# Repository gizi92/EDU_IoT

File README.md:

# EDU_IoT
## UBB IoT  project - Smart Office

### Project structure
- NodeMCU:
    - Up to date version: `/mcus/nodemcu/spi_master`
    - Example code snippets: `/mcus/nodemcu/examples/`
    - To run the examples, you need to install the following libraries:
        - LittleFS by lorol: https://github.com/lorol/LITTLEFS
        - ESP8266WiFi: https://github.com/esp8266/Arduino/tree/master/libraries/ESP8266WiFi
        - ESPAsyncTCP by me-no-dev: https://github.com/me-no-dev/ESPAsyncTCP
        - ESPAsyncWebServer by me-no-dev: https://github.com/me-no-dev/ESPAsyncWebServer
        - Arduino_JSON by arduino-libraries: https://github.com/arduino-libraries/Arduino_JSON
        - PubSubClient by knolleary: https://github.com/knolleary/pubsubclient

- Arduino Uno:
    - Up to date version: `/mcus/arduino_uno/spi_slave`
    - Example code snippets: `/mcus/arduino_uno/examples/`
    - To run the examples, you need to install the following libraries:
        - LiquidCrystal I2C by Marco Schwartz: https://github.com/johnrickman/LiquidCrystal_I2C
        - Arduino-DS3231 by Korneliusz Jarzebski: https://github.com/jarzebski/Arduino-DS3231
        - SimpleDHT by Winlin: https://github.com/winlinvip/SimpleDHT
        - Adafruit_TSL2561 by Adafruit: https://github.com/adafruit/Adafruit_TSL2561
        - Arduino-IRRemote by Arduino: https://github.com/Arduino-IRremote/Arduino-IRremote
- Libraries:
    - path: /mcus/libraries
    - Usage instructions:
        - Windows: Copy all folders from `/mcus/libraries` to your local `/Documents/Arduino/libraries/` folder. Reopen your arduino IDE. You should see the libraries under the `Sketch->Include Library` menu item of the IDE.
        - Other OSes: check where the user libraries for arduino are stored and copy the content of `/mcus/libraries/` there (Imma captain obvious). Alternatively you can create zip archives from the libraries (for ex `EDU_IoT_DataPacket.zip`) and import them into
        the Arduino IDE by using the `Sketch->Include Library->Add .ZIP Library...` function.

# Tools
- If you want to use VSCode for Arduino: https://www.youtube.com/watch?v=FnEvJXpxxNM&t=300s
- PlatformIO is a cool VSCode plugin for embedded programming: https://randomnerdtutorials.com/vs-code-platformio-ide-esp32-esp8266-arduino/
- vagrant and virtualbox for mqtt server.

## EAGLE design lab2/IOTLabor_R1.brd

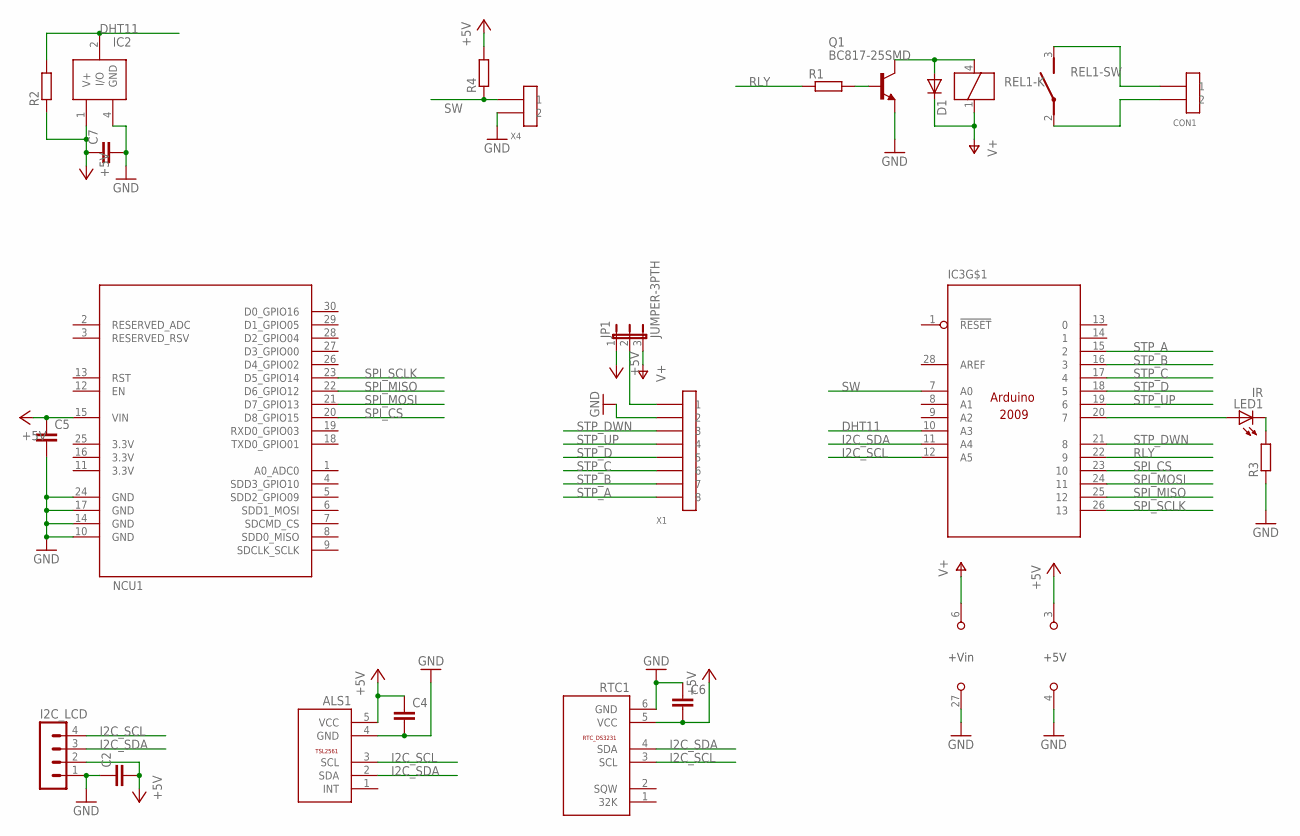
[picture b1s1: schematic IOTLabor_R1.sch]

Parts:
ALS1: TSL2561
C2, C4, C5, C6, C7: C-EUC0805K; C0805K
CON1: 2EDGVC-5.0-02P
D1: DIODE-MICROMELF-W; MICROMELF-W
I2C_LCD: MA04-1
IC2: DHT11V
IC3: ARDUINO2009_20; ARDUINO2009
JP1: JUMPER-3PTH; 1X03
LED1: IR; LED3MM
NCU1: NODEMCU8266
Q1: BC817-25SMD; SOT23-BEC
R1, R2, R3, R4: R-EU_R0805; R0805
REL1: 0J-SS-112
RTC1: RTC_DS3231; RTC
X1: 15EDG-8PV; 15EDGVC-3.5-08P
X4: 15EDG-2PV; 15EDGVC-3.5-02P

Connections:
3.3V: NCU1.11 (3.3V), NCU1.16 (3.3V), NCU1.25 (3.3V)
+3V3: IC3.2 (+3V3)
+5V: ALS1.5 (VCC), C2.2, C4.1, C5.1, C6.2, C7.1, I2C_LCD.2, IC2.1 (V+), IC3.3 (+5V), JP1.1, NCU1.15 (VIN), R2.1, R4.2, RTC1.5 (VCC)
DHT11: IC2.2 (I/O), IC3.10 (A3), R2.2
GND: ALS1.4 (GND), C2.1, C4.2, C5.2, C6.1, C7.2, I2C_LCD.1, IC2.4 (GND), IC3.4 (GND), IC3.5 (GND), IC3.27 (GND), NCU1.10 (GND), NCU1.14 (GND), NCU1.17 (GND), NCU1.24 (GND), Q1.E, R3.1, RTC1.6 (GND), X1.2, X4.2
I2C_SCL: ALS1.3 (SCL), I2C_LCD.4, IC3.12 (A5), RTC1.3 (SCL)
I2C_SDA: ALS1.2 (SDA), I2C_LCD.3, IC3.11 (A4), RTC1.4 (SDA)
unnamed: CON1.1, REL1.3
unnamed: CON1.2, REL1.2
unnamed: IC3.20 (7), LED1.A
unnamed: D1.A, Q1.C, REL1.4
unnamed: Q1.B, R1.2
unnamed: LED1.K (C), R3.2
unnamed: JP1.2, X1.1
RLY: IC3.22 (9), R1.1
SPI_CS: IC3.23 (10), NCU1.20 (D8_GPIO15)
SPI_MISO: IC3.25 (12), NCU1.22 (D6_GPIO12)
SPI_MOSI: IC3.24 (11), NCU1.21 (D7_GPIO13)
SPI_SCLK: IC3.26 (13), NCU1.23 (D5_GPIO14)
STP_A: IC3.15 (2), X1.8
STP_B: IC3.16 (3), X1.7
STP_C: IC3.17 (4), X1.6
STP_D: IC3.18 (5), X1.5
STP_DWN: IC3.21 (8), X1.3
STP_UP: IC3.19 (6), X1.4
SW: IC3.7 (A0), R4.1, X4.1
V+: D1.C, IC3.6 (+VIN), JP1.3, REL1.1

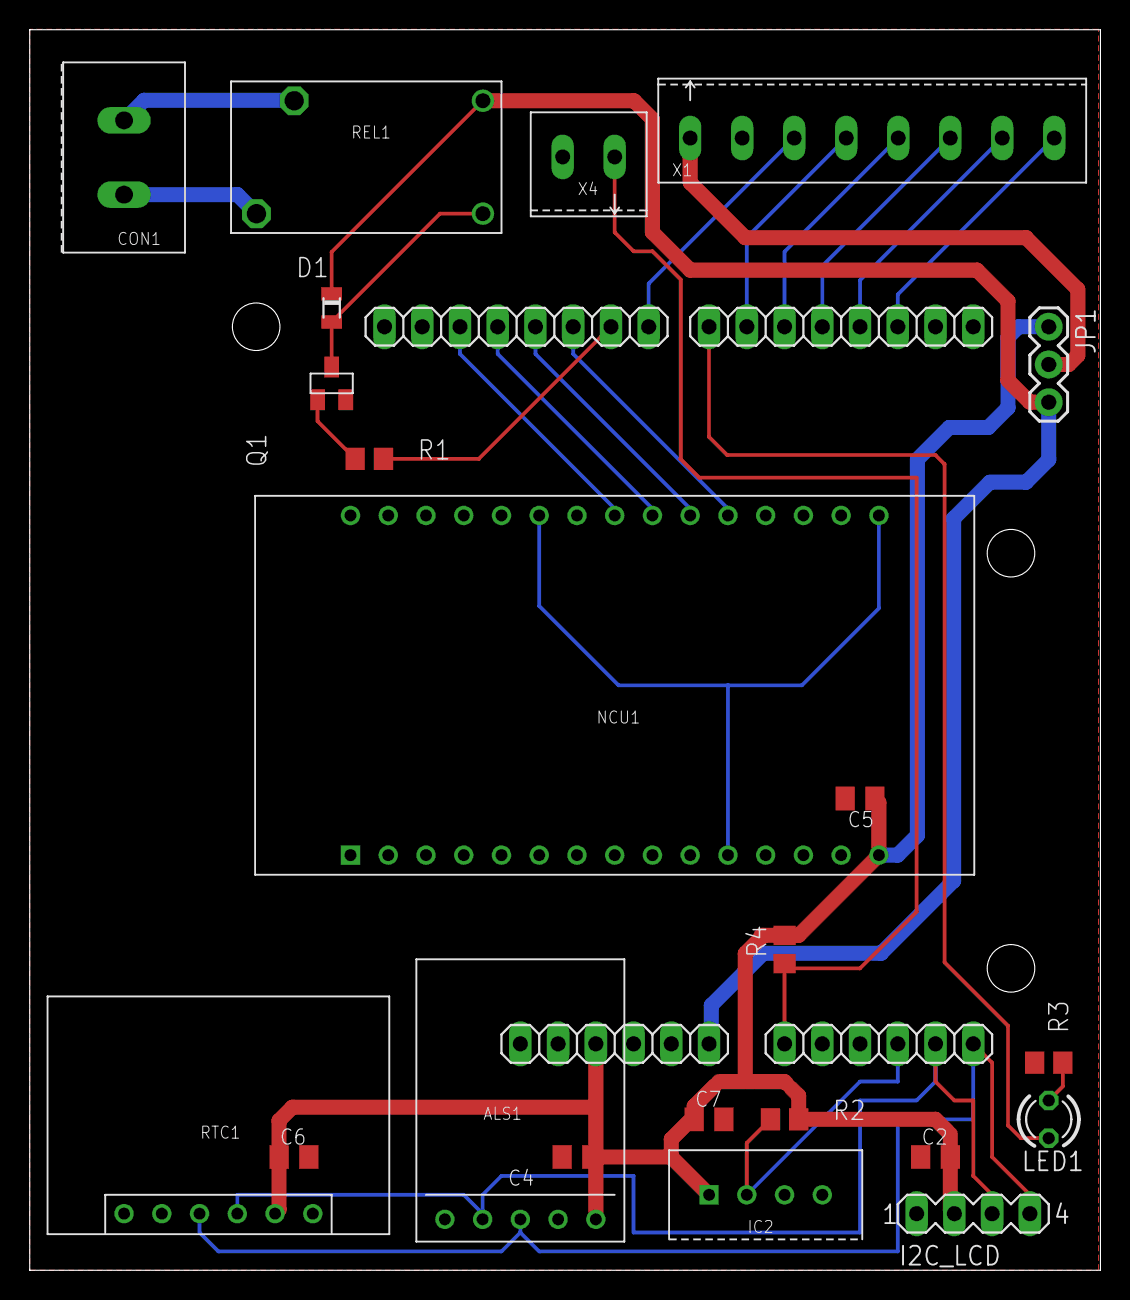
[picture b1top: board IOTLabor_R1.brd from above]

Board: 2 copper layers, 72.1 x 83.5 mm, 23 parts (0 on the bottom side), 26 nets.

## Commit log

2021-10-22 Lacika current status, TODO swap to SPI
2021-10-22 led controll and light sensor value read
2021-10-24 organizing mcus folder, add SPI debug inos, halfway there
2021-10-24 completed with LED
2021-10-24 refactored slave to use full dublex communication
2021-10-24 refactor master and slave for SPI, added LED test
2021-11-02 Added node webserver example program
2021-11-02 NodeWebServer now serves HTML with a bütön
2021-11-02 project cleanup and create libraries, see readme
2021-11-13 Lab 2 - Version 1 - by Marianna
2022-01-06 housing design for the smart office project
2022-01-23 DHT11, LightSensor, LCD, LightSwitch
2022-01-23 examples
2022-01-23 update readme with library information
2022-01-24 add all datapackets without stepper
2022-01-24 added frontend files
2022-01-25 spi_master gitignore for platformio project
2022-01-25 readme update
2022-01-25 platformIO project initialization
2022-01-25 redundant file removal
2022-01-27 swap webserver libraries
2022-01-30 webpage done, spi done, TODO IR led
2022-01-30 move ardu slave to platformio project
2022-01-30 done, dudes
2022-02-01 reorganizing workspace
2022-02-01 mqtt server as a bonus
2022-02-01 Create LICENSE
2022-02-01 cleanup
